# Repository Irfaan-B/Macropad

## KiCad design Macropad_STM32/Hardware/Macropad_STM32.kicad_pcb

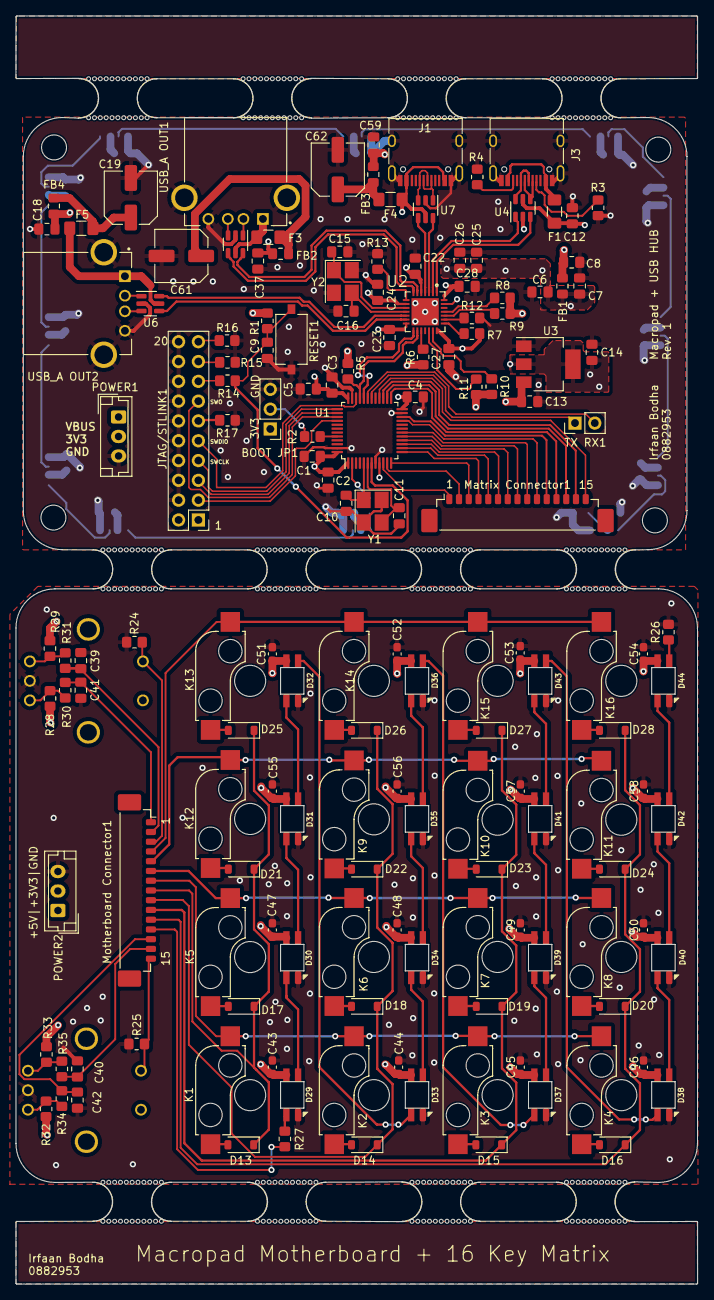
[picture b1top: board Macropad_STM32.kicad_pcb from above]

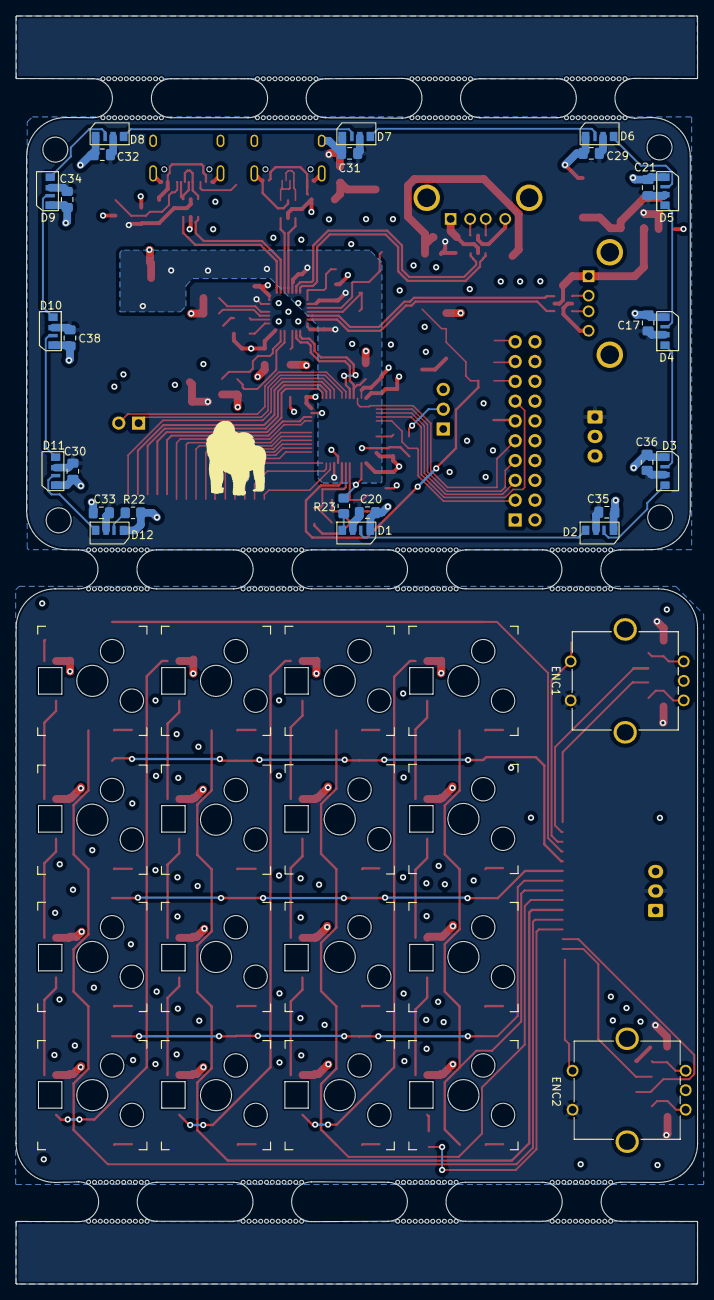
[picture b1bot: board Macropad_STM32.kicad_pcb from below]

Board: 4 copper layers, 87.4 x 162.6 mm, 199 parts (44 on the bottom side), 141 nets.

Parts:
BOOT JP1: Prog Jumper; PinHeader_1x03_P2.54mm_Vertical
C1, C2, C3, C4, C9, C17, C20, C21, C22, C23, C27, C29, C30, C31, C32, C33, C34, C35, C36, C38, C39, C40, C41, C42: 100n; C_0805_2012Metric_Pad1.18x1.45mm_HandSolder
C5, C12, C26: 10u; C_0805_2012Metric_Pad1.18x1.45mm_HandSolder
C6: 10n; C_0805_2012Metric_Pad1.18x1.45mm_HandSolder
C7, C8, C25, C28: 1u; C_0805_2012Metric_Pad1.18x1.45mm_HandSolder
C10, C11, C15, C16: 10p; C_0805_2012Metric_Pad1.18x1.45mm_HandSolder
C13, C14: 22u; C_0805_2012Metric_Pad1.18x1.45mm_HandSolder
C18, C37, C59: 2u2; C_0805_2012Metric_Pad1.18x1.45mm_HandSolder
C19, C61, C62: 100u; C_Elec_6.3x5.4
C24: locked; C_0805_2012Metric_Pad1.18x1.45mm_HandSolder
C43, C44, C45, C46, C47, C48, C49, C50, C51, C52, C53, C54, C55, C56, C57, C58: 100n; C_0603_1608Metric_Pad1.08x0.95mm_HandSolder
D1, D2, D3, D4, D5, D6, D7, D8, D9, D10, D11, D12: SK6812; SK6812SIDE
D13, D14, D15, D16, D17, D18, D19, D20, D21, D22, D23, D24, D25, D26, D27, D28: 1N4148; D_SOD-123
D29, D30, D31, D32, D33, D34, D35, D36, D37, D38, D39, D40, D41, D42, D43, D44: SK6812MINI; SK6812-MINI-E
ENC1, ENC2: EC11 Encoder; RotaryEncoder_Bourns_Vertical_PEC12R-3xxxF-Sxxxx
F1: 1A; Fuse_1206_3216Metric_Pad1.42x1.75mm_HandSolder
F3, F4, F5: 500mA; Fuse_1206_3216Metric_Pad1.42x1.75mm_HandSolder
FB1, FB2, FB3, FB4: 120R; Fuse_0805_2012Metric_Pad1.15x1.40mm_HandSolder
H1, H3, H4, H6: MountingHole; MountingHole_3.2mm_M3_DIN965
J1, J3: USB_C_Receptacle_USB2.0; USB_C_Receptacle_HRO_TYPE-C-31-M-12
J2, J8: USB_A; AMPHENOL_UE27AC54100
JTAG/STLINK1: JTAG; PinHeader_2x10_P2.54mm_Vertical
K1, K2, K3, K4, K5, K6, K7, K8, K9, K10, K11, K12, K13, K14, K15, K16: Kailh Hotswap Socket; Kailh_socket_MX_platemount
Matrix Connector1: 533981571; Molex_PicoBlade_53398-1571_1x15-1MP_P1.25mm_Vertical
Motherboard Connector1: 533981571; Molex_PicoBlade_53398-1571_1x15-1MP_P1.25mm_Vertical
POWER1, POWER2: Power Connector; JST_EH_B3B-EH-A_1x03_P2.50mm_Vertical
R1, R2, R6, R7, R8, R9, R10, R11, R12, R15, R16, R17: 10k; R_0805_2012Metric_Pad1.20x1.40mm_HandSolder
R3, R4: 5k1; R_0805_2012Metric_Pad1.20x1.40mm_HandSolder
R5: 1k5; R_0805_2012Metric_Pad1.20x1.40mm_HandSolder
R13: 649; R_0805_2012Metric_Pad1.20x1.40mm_HandSolder
R14: 0; R_0805_2012Metric_Pad1.20x1.40mm_HandSolder
R22, R23, R26, R27: 500; R_0805_2012Metric_Pad1.20x1.40mm_HandSolder
R24, R25, R28, R29, R30, R31, R32, R33, R34, R35: 10K; R_0805_2012Metric_Pad1.20x1.40mm_HandSolder
RESET1: SW_Push; SW_Tactile_SPST_NO_Straight_CK_PTS636Sx25SMTRLFS
TX RX1: Conn_01x02_Socket; PinHeader_1x02_P2.54mm_Vertical
U1: STM32F103C8T6; LQFP-48_7x7mm_P0.5mm
U2: CY7C65632-28LTXCT; QFN50P500X500X80-29N
U3: AMS1117-3.3; SOT-223-3_TabPin2
U4, U6, U7, U8: USBLC6-2SC6; SOT-23-6
Y1: 16MHz; Crystal_SMD_3225-4Pin_3.2x2.5mm_HandSoldering
Y2: 12MHz; Crystal_SMD_3225-4Pin_3.2x2.5mm_HandSoldering
mouse-bite-5mm-slot, mouse-bite-5mm-slot#2, mouse-bite-5mm-slot#3, mouse-bite-5mm-slot#4, mouse-bite-5mm-slot#5, mouse-bite-5mm-slot#6, mouse-bite-5mm-slot#7, mouse-bite-5mm-slot#8, mouse-bite-5mm-slot#9, mouse-bite-5mm-slot#10, mouse-bite-5mm-slot#11, mouse-bite-5mm-slot#12: VAL**; mouse-bite-5mm-slot

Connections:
+3.3V: BOOT JP1.1 (A), C1.1, C2.1, C3.1, C4.1, C5.1, C8.1, C14.1, C27.1, C28.1, FB1.2, JTAG/STLINK1.1 (VTREF), JTAG/STLINK1.2 (VCC/NC), POWER1.2, R1.1, R5.2, R6.1, R7.1, R8.1, R9.1, R10.1, R11.1, U1.1 (VBAT), U1.24 (VDD), U1.36 (VDD), U1.48 (VDD), U2.21 (VCC_D), U2.28 (VREG), U3.2 (VO)
+3.3VA: C6.1, C7.1, C22.1, C23.1, C24.1, C25.1, C26.1, FB1.1, U1.9 (VDDA), U2.5 (VCC_A), U2.9 (VCC_A), U2.14 (VCC_A)
+3V3: ENC1.S1, ENC2.S1, POWER2.2, R28.2, R29.1, R32.1, R33.1
+5V: C43.1, C44.1, C45.1, C46.1, C47.1, C48.1, C49.1, C50.1, C51.1, C52.1, C53.1, C54.1, C55.1, C56.1, C57.1, C58.1, D29.1 (VDD), D30.1 (VDD), D31.1 (VDD), D32.1 (VDD), D33.1 (VDD), D34.1 (VDD), D35.1 (VDD), D36.1 (VDD), D37.1 (VDD), D38.1 (VDD), D39.1 (VDD), D40.1 (VDD), D41.1 (VDD), D42.1 (VDD), D43.1 (VDD), D44.1 (VDD), POWER2.1
/BOOT0: R2.2, U1.44 (BOOT0)
/COL0: Matrix Connector1.7, U1.16 (PA6)
/COL1: Matrix Connector1.6, U1.15 (PA5)
/COL2: Matrix Connector1.5, U1.14 (PA4)
/COL3: Matrix Connector1.4, U1.13 (PA3)
/ENC1_A: Matrix Connector1.1, U1.10 (PA0)
/ENC1_B: Matrix Connector1.2, U1.11 (PA1)
/ENC1_SW: Matrix Connector1.3, U1.12 (PA2)
/ENC2_A: Matrix Connector1.13, U1.26 (PB13)
/ENC2_B: Matrix Connector1.14, U1.27 (PB14)
/ENC2_SW: Matrix Connector1.15, U1.28 (PB15)
/HSE_IN: C10.1, U1.5 (PD0), Y1.1
/HSE_OUT: C11.1, U1.6 (PD1), Y1.3
/JP_BOOT0: BOOT JP1.2 (C), R2.1
/Key_LED: Matrix Connector1.12, U1.25 (PB12)
/LED: R23.1, U1.2 (PC13)
/LED0: D4.3 (DOUT), D5.1 (DIN)
/LED1: D8.3 (DOUT), D9.1 (DIN)
/Matrix/COL0: K1.1, K2.1, K3.1, K4.1, Motherboard Connector1.7
/Matrix/COL1: K5.1, K6.1, K7.1, K8.1, Motherboard Connector1.6
/Matrix/COL2: K9.1, K10.1, K11.1, K12.1, Motherboard Connector1.5
/Matrix/COL3: K13.1, K14.1, K15.1, K16.1, Motherboard Connector1.4
/Matrix/ENC_1_A: C41.1, Motherboard Connector1.1, R30.2
/Matrix/ENC_1_B: C39.1, Motherboard Connector1.2, R31.2
/Matrix/ENC_1_SW: ENC1.S2, Motherboard Connector1.3, R24.2
/Matrix/ENC_2_A: C42.1, Motherboard Connector1.13, R34.2
/Matrix/ENC_2_B: C40.1, Motherboard Connector1.14, R35.2
/Matrix/ENC_2_SW: ENC2.S2, Motherboard Connector1.15, R25.2
/Matrix/Key_LED: Motherboard Connector1.12, R27.1
/Matrix/LED45: D32.2 (DOUT), D33.4 (DIN)
/Matrix/LED89: D36.2 (DOUT), D37.4 (DIN)
/Matrix/LED1213: D38.4 (DIN), D43.2 (DOUT)
/Matrix/ROW0: D13.1 (K), D17.1 (K), D21.1 (K), D25.1 (K), Motherboard Connector1.8
/Matrix/ROW1: D14.1 (K), D18.1 (K), D22.1 (K), D26.1 (K), Motherboard Connector1.9
/Matrix/ROW2: D15.1 (K), D19.1 (K), D23.1 (K), D27.1 (K), Motherboard Connector1.10
/Matrix/ROW3: D16.1 (K), D20.1 (K), D24.1 (K), D28.1 (K), Motherboard Connector1.11
/NRST: C9.1, R1.2, R14.2, RESET1.1, U1.7 (NRST)
/ROW0: Matrix Connector1.8, U1.17 (PA7)
/ROW1: Matrix Connector1.9, U1.18 (PB0)
/ROW2: Matrix Connector1.10, U1.21 (PB10)
/ROW3: Matrix Connector1.11, U1.22 (PB11)
/SWCLK: JTAG/STLINK1.7 (TMS/SWDIO), U1.37 (PA14)
/SWDIO: JTAG/STLINK1.9 (TCK/SWDCLK), U1.34 (PA13)
/SWO: JTAG/STLINK1.13 (TDO/SWO), U1.39 (PB3)
/TDI: JTAG/STLINK1.5 (TDI), U1.38 (PA15)
/UP_USB_D+: U2.2 (D+), U4.1 (IO1)
/UP_USB_D-: U2.1 (D–), U4.3 (IO2)
/USBHUB/D1_D+: U2.4 (DD+1), U7.4 (IO2)
/USBHUB/D1_D-: U2.3 (DD–1), U7.6 (IO1)
/USBHUB/D1_VBUS: F3.1, J2.1 (VBUS), U8.5 (VBUS)
/USBHUB/D2_D+: U2.7 (DD+2), U8.4 (IO2)
/USBHUB/D2_D-: U2.6 (DD–2), U8.6 (IO1)
/USBHUB/D2_VBUS: F5.1, J8.1 (VBUS), U6.5 (VBUS)
/USBHUB/D3_D+: U2.13 (DD+3), U6.4 (IO2)
/USBHUB/D3_D-: U2.12 (DD–3), U6.6 (IO1)
/USBHUB/D3_VBUS: F4.1, J1.A4 (VBUS), J1.A9 (VBUS), J1.B4 (VBUS), J1.B9 (VBUS), U7.5 (VBUS)
/USBHUB/USB_SELFPWR: R7.2, U2.22 (SELFPWR)
/USBHUB/USB_XIN: C15.1, U2.10 (XIN), Y2.1
/USBHUB/USB_XOUT: C16.1, U2.11 (XOUT), Y2.3
/USBHUB/USB_nRST: R6.2, U2.17 (~RESET)
/USBHUB/nOVR1: R8.2, U2.25 (~OVR~1)
/USBHUB/nOVR2: R9.2, U2.24 (~OVR~2)
/USBHUB/nOVR3: R10.2, U2.20 (~OVR~3)
/USBHUB/nOVR4: R11.2, U2.19 (~OVR~4)
/USB_DN_D+: R5.1, U1.33 (PA12), U2.16 (DD+4)
/USB_DN_D-: U1.32 (PA11), U2.15 (DD–4)
/USB_UP_D+: J3.A6 (D+), J3.B6 (D+), U4.6 (IO1)
/USB_UP_D-: J3.A7 (D-), J3.B7 (D-), U4.4 (IO2)
/sRST: JTAG/STLINK1.15 (~SRST), R14.1
/tRST: JTAG/STLINK1.3 (~TRST), U1.40 (PB4)
GND: BOOT JP1.3 (B), C1.2, C2.2, C3.2, C4.2, C5.2, C6.2, C7.2, C8.2, C9.2, C10.2, C11.2, C12.1, C13.2, C14.2, C15.2, C16.2, C17.2, C18.2, C19.2, C20.2, C21.2, C22.2, C23.2, C24.2, C25.2, C26.2, C27.2, C28.2, C29.2, C30.2, C31.2, C32.2, C33.2, C34.2, C35.2, C36.2, C37.2, C38.2, C59.2, C61.2, C62.2, D1.4 (VSS), D2.4 (VSS), D3.4 (VSS), D4.4 (VSS), D5.4 (VSS), D6.4 (VSS), D7.4 (VSS), D8.4 (VSS), D9.4 (VSS), D10.4 (VSS), D11.4 (VSS), D12.4 (VSS), J1.A1 (GND), J1.A12 (GND), J1.B1 (GND), J1.B12 (GND), J1.S1 (SHIELD), J2.4 (GND), J2.5 (Shield), J3.A1 (GND), J3.A12 (GND), J3.B1 (GND), J3.B12 (GND), J3.S1 (SHIELD), J8.4 (GND), J8.5 (Shield), JTAG/STLINK1.4 (GND), JTAG/STLINK1.6 (GND), JTAG/STLINK1.8 (GND), JTAG/STLINK1.10 (GND), JTAG/STLINK1.12 (GND), JTAG/STLINK1.14 (GND), JTAG/STLINK1.16 (GND), JTAG/STLINK1.18 (GND), JTAG/STLINK1.20 (GND), POWER1.3, R3.2, R4.2, R12.1, R13.2, R15.2, R16.2, R17.2, R22.2, RESET1.2, U1.8 (VSSA), U1.23 (VSS), U1.35 (VSS), U1.47 (VSS), U2.29 (GND), U3.1 (GND), U4.2 (GND), U6.2 (GND), U7.2 (GND), U8.2 (GND), Y1.2, Y1.4, Y2.2, Y2.4
GND1: C39.2, C40.2, C41.2, C42.2, C43.2, C44.2, C45.2, C46.2, C47.2, C48.2, C49.2, C50.2, C51.2, C52.2, C53.2, C54.2, C55.2, C56.2, C57.2, C58.2, D29.3 (VSS), D30.3 (VSS), D31.3 (VSS), D32.3 (VSS), D33.3 (VSS), D34.3 (VSS), D35.3 (VSS), D36.3 (VSS), D37.3 (VSS), D38.3 (VSS), D39.3 (VSS), D40.3 (VSS), D41.3 (VSS), D42.3 (VSS), D43.3 (VSS), D44.3 (VSS), ENC1.C, ENC2.C, POWER2.3, R24.1, R25.1, R26.2
unnamed: C19.1, F5.2, FB4.1
unnamed: C61.1, F3.2, FB2.1
unnamed: C62.1, F4.2, FB3.1
unnamed: D1.1 (DIN), R23.2
unnamed: D1.3 (DOUT), D2.1 (DIN)
unnamed: D2.3 (DOUT), D3.1 (DIN)
unnamed: D3.3 (DOUT), D4.1 (DIN)
unnamed: D5.3 (DOUT), D6.1 (DIN)
unnamed: D6.3 (DOUT), D7.1 (DIN)
unnamed: D7.3 (DOUT), D8.1 (DIN)
unnamed: D9.3 (DOUT), D10.1 (DIN)
unnamed: D10.3 (DOUT), D11.1 (DIN)
unnamed: D11.3 (DOUT), D12.1 (DIN)
unnamed: D12.3 (DOUT), R22.1
unnamed: D13.2 (A), K1.2
unnamed: D14.2 (A), K2.2
unnamed: D15.2 (A), K3.2
unnamed: D16.2 (A), K4.2
unnamed: D17.2 (A), K5.2
unnamed: D18.2 (A), K6.2
unnamed: D19.2 (A), K7.2
unnamed: D20.2 (A), K8.2
unnamed: D21.2 (A), K12.2
unnamed: D22.2 (A), K9.2
unnamed: D23.2 (A), K10.2
unnamed: D24.2 (A), K11.2
unnamed: D25.2 (A), K13.2
unnamed: D26.2 (A), K14.2
unnamed: D27.2 (A), K15.2
unnamed: D28.2 (A), K16.2
unnamed: D29.4 (DIN), R27.2
unnamed: D29.2 (DOUT), D30.4 (DIN)
unnamed: D30.2 (DOUT), D31.4 (DIN)
unnamed: D31.2 (DOUT), D32.4 (DIN)
unnamed: D33.2 (DOUT), D34.4 (DIN)
unnamed: D34.2 (DOUT), D35.4 (DIN)
unnamed: D35.2 (DOUT), D36.4 (DIN)
unnamed: D37.2 (DOUT), D39.4 (DIN)
unnamed: D38.2 (DOUT), D40.4 (DIN)
unnamed: D39.2 (DOUT), D41.4 (DIN)
unnamed: D40.2 (DOUT), D42.4 (DIN)
unnamed: D41.2 (DOUT), D43.4 (DIN)
unnamed: D42.2 (DOUT), D44.4 (DIN)
unnamed: D44.2 (DOUT), R26.1
unnamed: ENC1.A, R28.1, R30.1
unnamed: ENC1.B, R29.2, R31.1
unnamed: ENC2.A, R32.2, R34.1
unnamed: ENC2.B, R33.2, R35.1
unnamed: F1.1, J3.A4 (VBUS), J3.A9 (VBUS), J3.B4 (VBUS), J3.B9 (VBUS)
unnamed: J1.A6 (D+), J1.B6 (D+), U7.3 (IO2)
unnamed: J1.A7 (D-), J1.B7 (D-), U7.1 (IO1)
unnamed: J2.3 (D+), U8.3 (IO2)
unnamed: J2.2 (D-), U8.1 (IO1)
unnamed: J3.A5 (CC1), R3.1
unnamed: J3.B5 (CC2), R4.1
unnamed: J8.3 (D+), U6.3 (IO2)
unnamed: J8.2 (D-), U6.1 (IO1)
unnamed: JTAG/STLINK1.19 (DBGACK/NC), R16.1
unnamed: JTAG/STLINK1.17 (DBGRQ/NC), R15.1
unnamed: JTAG/STLINK1.11 (RTCK), R17.1
unnamed: TX RX1.1, U1.30 (PA9)
unnamed: TX RX1.2, U1.31 (PA10)
unnamed: R12.2, U2.23 (GANG)
unnamed: R13.1, U2.8 (RREF)
VBUS: C12.2, C13.1, C17.1, C18.1, C20.1, C21.1, C29.1, C30.1, C31.1, C32.1, C33.1, C34.1, C35.1, C36.1, C37.1, C38.1, C59.1, D1.2 (VDD), D2.2 (VDD), D3.2 (VDD), D4.2 (VDD), D5.2 (VDD), D6.2 (VDD), D7.2 (VDD), D8.2 (VDD), D9.2 (VDD), D10.2 (VDD), D11.2 (VDD), D12.2 (VDD), F1.2, FB2.2, FB3.2, FB4.2, POWER1.1, U2.27 (VCC), U3.3 (VI), U4.5 (VBUS)

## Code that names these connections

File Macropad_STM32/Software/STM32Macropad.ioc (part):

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Mcu.Name=STM32F103C(8-B)Tx
Mcu.Package=LQFP48
Mcu.UserName=STM32F103C8Tx
PA0-WKUP.Signal=GPIO_Input
PA1.Signal=GPIO_Input
PA11.Mode=Device
PA11.Signal=USB_DM
PA12.Mode=Device
PA12.Signal=USB_DP
PA13.Mode=Serial_Wire
PA13.Signal=SYS_JTMS-SWDIO
PA14.Mode=Serial_Wire
PA14.Signal=SYS_JTCK-SWCLK
PA2.Signal=GPIO_Input
PA3.Signal=GPIO_Output
PA4.Signal=GPIO_Output
PA5.Signal=GPIO_Output
PA6.GPIOParameters=GPIO_PuPd,GPIO_Label
PA6.GPIO_Label=ROW0
PA6.GPIO_PuPd=GPIO_PULLUP
PA6.Signal=GPIO_Input
PA7.GPIOParameters=GPIO_PuPd,GPIO_Label
PA7.GPIO_Label=ROW1
PA7.GPIO_PuPd=GPIO_PULLUP
PA7.Signal=GPIO_Input
PB10.GPIOParameters=GPIO_PuPd,GPIO_Label
PB10.GPIO_Label=ROW3
PB10.GPIO_PuPd=GPIO_PULLUP
PB10.Signal=GPIO_Input
PB12.Signal=GPIO_Output
PB13.Signal=GPIO_Input
PB14.Signal=GPIO_Input
PB15.Signal=GPIO_Input
PB2.GPIOParameters=GPIO_PuPd,GPIO_Label
PB2.GPIO_Label=ROW2
PB2.GPIO_PuPd=GPIO_PULLUP
PB2.Signal=GPIO_Input
PC13-TAMPER-RTC.GPIOParameters=GPIO_Label
PC13-TAMPER-RTC.GPIO_Label=LED
PC13-TAMPER-RTC.Signal=GPIO_Output
PD0-OSC_IN.Mode=HSE-External-Oscillator
PD0-OSC_IN.Signal=RCC_OSC_IN
PD1-OSC_OUT.Mode=HSE-External-Oscillator
PD1-OSC_OUT.Signal=RCC_OSC_OUT
RCC.HSEDivPLL=RCC_HSE_PREDIV_DIV2
RCC.HSE_VALUE=16000000
RCC.SYSCLKFreq_VALUE=72000000
RCC.SYSCLKSource=RCC_SYSCLKSOURCE_PLLCLK
board=custom

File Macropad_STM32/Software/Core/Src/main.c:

/* Includes ------------------------------------------------------------------*/
#include "main.h"
#include "usb_device.h"
#include "led.h"
#include "keypad.h"

/* Private includes ----------------------------------------------------------*/
/* USER CODE BEGIN Includes */

/* USER CODE END Includes */

/* Private typedef -----------------------------------------------------------*/
/* USER CODE BEGIN PTD */

/* USER CODE END PTD */

/* Private define ------------------------------------------------------------*/
/* USER CODE BEGIN PD */

// Define the timing constants (in clock cycles)
#define T0H  1  // 0.32 µs
#define T1H  3  // 0.64 µs
#define T0L  3   // 0.8 µs
#define T1L  1   // 0.2 µs
#define TRST 5000    // >80 µs

/* USER CODE END PD */

/* Private macro -------------------------------------------------------------*/
/* USER CODE BEGIN PM */

/* USER CODE END PM */

/* Private variables ---------------------------------------------------------*/

/* USER CODE BEGIN PV */
uint16_t led_data[NUM_LEDS][3]; // Assuming 24 bits per LED
/* USER CODE END PV */

/* Private function prototypes -----------------------------------------------*/
void SystemClock_Config(void);
static void MX_GPIO_Init(void);
/* USER CODE BEGIN PFP */
/* USER CODE END PFP */

/* Private user code ---------------------------------------------------------*/
/* USER CODE BEGIN 0 */
void cycle_colors(void) {
    static uint8_t color_index = 0;
    uint8_t colors[3][3] = {
        {255, 0, 0},   // Red
        {0, 255, 0},   // Green
        {0, 0, 255}    // Blue
    };

    for (uint8_t i = 0; i < NUM_LEDS; i++) {
        set_led_color(i, colors[color_index][0], colors[color_index][1], colors[color_index][2]);
    }

    color_index = (color_index + 1) % 3;
}
/* USER CODE END 0 */

/**
  * @brief  The application entry point.
  * @retval int
  */
int main(void)
{
    /* USER CODE BEGIN 1 */
    __set_CONTROL(0);
    __ISB();

    /* USER CODE END 1 */

    /* MCU Configuration--------------------------------------------------------*/

    /* Reset of all peripherals, Initializes the Flash interface and the Systick. */
    HAL_Init();

    /* USER CODE BEGIN Init */

    /* USER CODE END Init */

    /* Configure the system clock */
    SystemClock_Config();

    /* USER CODE BEGIN SysInit */

    /* USER CODE END SysInit */

    /* Initialize all configured peripherals */
    MX_GPIO_Init();
    MX_USB_DEVICE_Init();
    /* USER CODE BEGIN 2 */
    for (uint8_t i = 0; i < NUM_LEDS; i++) 
    {
      set_led_color(i, 255, 0, 0); // Set all LEDs to red
    }

    char key;

    /* USER CODE END 2 */

    /* Infinite loop */
    /* USER CODE BEGIN WHILE */
    while (1)
    {
      key = Keypad_Scan();

      if (key != '\0')
      {
        Keypad_SendKeyViaUSB(key);
        HAL_Delay(150);
      }
      // __disable_irq();
      // cycle_colors(); // Cycle through colors
      // update_leds(); // Update all LEDs
      // __enable_irq();
      // HAL_Delay(1000);
    /* USER CODE END WHILE */
    }
    /* USER CODE BEGIN 3 */
    /* USER CODE END 3 */
}

/**
  * @brief System Clock Configuration
  * @retval None
  */
void SystemClock_Config(void)
{
  RCC_OscInitTypeDef RCC_OscInitStruct = {0};
  RCC_ClkInitTypeDef RCC_ClkInitStruct = {0};
  RCC_PeriphCLKInitTypeDef PeriphClkInit = {0};

  /** Initializes the RCC Oscillators according to the specified parameters
  * in the RCC_OscInitTypeDef structure.
  */
  RCC_OscInitStruct.OscillatorType = RCC_OSCILLATORTYPE_HSE;
  RCC_OscInitStruct.HSEState = RCC_HSE_ON;
  RCC_OscInitStruct.HSEPredivValue = RCC_HSE_PREDIV_DIV2;
  RCC_OscInitStruct.HSIState = RCC_HSI_ON;
  RCC_OscInitStruct.PLL.PLLState = RCC_PLL_ON;
  RCC_OscInitStruct.PLL.PLLSource = RCC_PLLSOURCE_HSE;
  RCC_OscInitStruct.PLL.PLLMUL = RCC_PLL_MUL9;
  if (HAL_RCC_OscConfig(&RCC_OscInitStruct) != HAL_OK)
  {
    Error_Handler();
  }

  /** Initializes the CPU, AHB and APB buses clocks
  */
  RCC_ClkInitStruct.ClockType = RCC_CLOCKTYPE_HCLK|RCC_CLOCKTYPE_SYSCLK
                              |RCC_CLOCKTYPE_PCLK1|RCC_CLOCKTYPE_PCLK2;
  RCC_ClkInitStruct.SYSCLKSource = RCC_SYSCLKSOURCE_PLLCLK;
  RCC_ClkInitStruct.AHBCLKDivider = RCC_SYSCLK_DIV1;
  RCC_ClkInitStruct.APB1CLKDivider = RCC_HCLK_DIV2;
  RCC_ClkInitStruct.APB2CLKDivider = RCC_HCLK_DIV1;

  if (HAL_RCC_ClockConfig(&RCC_ClkInitStruct, FLASH_LATENCY_2) != HAL_OK)
  {
    Error_Handler();
  }
  PeriphClkInit.PeriphClockSelection = RCC_PERIPHCLK_USB;
  PeriphClkInit.UsbClockSelection = RCC_USBCLKSOURCE_PLL_DIV1_5;
  if (HAL_RCCEx_PeriphCLKConfig(&PeriphClkInit) != HAL_OK)
  {
    Error_Handler();
  }
}

/**
  * @brief GPIO Initialization Function
  * @param None
  * @retval None
  */
static void MX_GPIO_Init(void)
{
  GPIO_InitTypeDef GPIO_InitStruct = {0};
/* USER CODE BEGIN MX_GPIO_Init_1 */
/* USER CODE END MX_GPIO_Init_1 */

  /* GPIO Ports Clock Enable */
  __HAL_RCC_GPIOC_CLK_ENABLE();
  __HAL_RCC_GPIOD_CLK_ENABLE();
  __HAL_RCC_GPIOA_CLK_ENABLE();
  __HAL_RCC_GPIOB_CLK_ENABLE();

  /*Configure GPIO pin Output Level */
  HAL_GPIO_WritePin(LED_GPIO_Port, LED_Pin, GPIO_PIN_RESET);

  /*Configure GPIO pin Output Level */
  HAL_GPIO_WritePin(GPIOA, GPIO_PIN_3|GPIO_PIN_4|GPIO_PIN_5, GPIO_PIN_RESET);

  /*Configure GPIO pin Output Level */
  HAL_GPIO_WritePin(GPIOB, GPIO_PIN_12, GPIO_PIN_RESET);

  /*Configure GPIO pin : LED_Pin */
  GPIO_InitStruct.Pin = LED_Pin;
  GPIO_InitStruct.Mode = GPIO_MODE_OUTPUT_PP;
  GPIO_InitStruct.Pull = GPIO_NOPULL;
  GPIO_InitStruct.Speed = GPIO_SPEED_FREQ_HIGH;
  HAL_GPIO_Init(LED_GPIO_Port, &GPIO_InitStruct);

  /*Configure GPIO pins : PA0 PA1 PA2 */
  GPIO_InitStruct.Pin = GPIO_PIN_0|GPIO_PIN_1|GPIO_PIN_2;
  GPIO_InitStruct.Mode = GPIO_MODE_INPUT;
  GPIO_InitStruct.Pull = GPIO_NOPULL;
  HAL_GPIO_Init(GPIOA, &GPIO_InitStruct);

  /*Configure GPIO pins : PA3 PA4 PA5 PA6 */
  GPIO_InitStruct.Pin = COL3_Pin|COL2_Pin|COL1_Pin|COL0_Pin;
  GPIO_InitStruct.Mode = GPIO_MODE_OUTPUT_PP;
  GPIO_InitStruct.Pull = GPIO_NOPULL;
  GPIO_InitStruct.Speed = GPIO_SPEED_FREQ_LOW;
  HAL_GPIO_Init(GPIOA, &GPIO_InitStruct);
  HAL_GPIO_WritePin(GPIOA, COL3_Pin | COL2_Pin | COL1_Pin | COL0_Pin, GPIO_PIN_SET);

  /*Configure GPIO pins : ROW0_Pin ROW1_Pin */
  GPIO_InitStruct.Pin = ROW0_Pin;
  GPIO_InitStruct.Mode = GPIO_MODE_INPUT;
  GPIO_InitStruct.Pull = GPIO_PULLUP;
  HAL_GPIO_Init(GPIOA, &GPIO_InitStruct);

  /*Configure GPIO pins : ROW2_Pin ROW3_Pin */
  GPIO_InitStruct.Pin = ROW1_Pin|ROW2_Pin|ROW3_Pin;
  GPIO_InitStruct.Mode = GPIO_MODE_INPUT;
  GPIO_InitStruct.Pull = GPIO_PULLUP;
  HAL_GPIO_Init(GPIOB, &GPIO_InitStruct);

  /*Configure GPIO pin : PB12 */
  GPIO_InitStruct.Pin = GPIO_PIN_12;
  GPIO_InitStruct.Mode = GPIO_MODE_OUTPUT_PP;
  GPIO_InitStruct.Pull = GPIO_NOPULL;
  GPIO_InitStruct.Speed = GPIO_SPEED_FREQ_LOW;
  HAL_GPIO_Init(GPIOB, &GPIO_InitStruct);

  /*Configure GPIO pins : PB13 PB14 PB15 */
  GPIO_InitStruct.Pin = GPIO_PIN_13|GPIO_PIN_14|GPIO_PIN_15;
  GPIO_InitStruct.Mode = GPIO_MODE_INPUT;
  GPIO_InitStruct.Pull = GPIO_NOPULL;
  HAL_GPIO_Init(GPIOB, &GPIO_InitStruct);

/* USER CODE BEGIN MX_GPIO_Init_2 */
/* USER CODE END MX_GPIO_Init_2 */
}

/* USER CODE BEGIN 4 */

/* USER CODE END 4 */

/**
  * @brief  This function is executed in case of error occurrence.
  * @retval None
  */
void Error_Handler(void)
{
  /* USER CODE BEGIN Error_Handler_Debug */
  /* User can add his own implementation to report the HAL error return state */
  __disable_irq();
  while (1)
  {
  }
  /* USER CODE END Error_Handler_Debug */
}

#ifdef  USE_FULL_ASSERT
/**
  * @brief  Reports the name of the source file and the source line number
  *         where the assert_param error has occurred.
  * @param  file: pointer to the source file name
  * @param  line: assert_param error line source number
  * @retval None
  */
void assert_failed(uint8_t *file, uint32_t line)
{
  /* USER CODE BEGIN 6 */
  /* User can add his own implementation to report the file name and line number,
     ex: printf("Wrong parameters value: file %s on line %d\r\n", file, line) */
  /* USER CODE END 6 */
}
#endif /* USE_FULL_ASSERT */

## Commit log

2023-11-02 Working on USB Hub
2023-11-03 USB Hub & Jtag connectors added Todo: - Keypad matrix - Rotary encoders - PCB
2023-11-03 .gitignore working?
2023-11-03 added .gitignore
2023-11-03 .gitignore fixed
2023-11-04 Finished main schematic (excl. matrix)
2023-11-05 Matrix PCB layout done
2023-11-05 updated gitignore
2023-11-05 Finished PCB layout, TODO: traces
2023-12-10 Schematic changes Motherboard nearing completion
2023-12-10 Minor changes to motherboard
2023-12-11 Revision 1 nearly finished
2023-12-28 Nearly finished Todo: - Fix silkscreen - Final check
2024-01-28 Hardware finished and motherboard has been tested. Todo: Test keyboard matrix and write firmware.
2024-08-16 Cleaned up repo, added software folder
2024-08-16 Clean up
2024-08-16 c cpp properties added
2024-08-16 Can now program & flash the mcu without using stm32cubeide. yippee!
2024-08-16 fixed SWD
2024-08-16 LED software added
2024-08-17 Make working in vscode, leds not. Fix soon?
2024-08-17 fixed everything.. somehow..
2024-08-17 Debugging in vscode working
2024-08-19 Keypad functions working, hardware needs adjusting
